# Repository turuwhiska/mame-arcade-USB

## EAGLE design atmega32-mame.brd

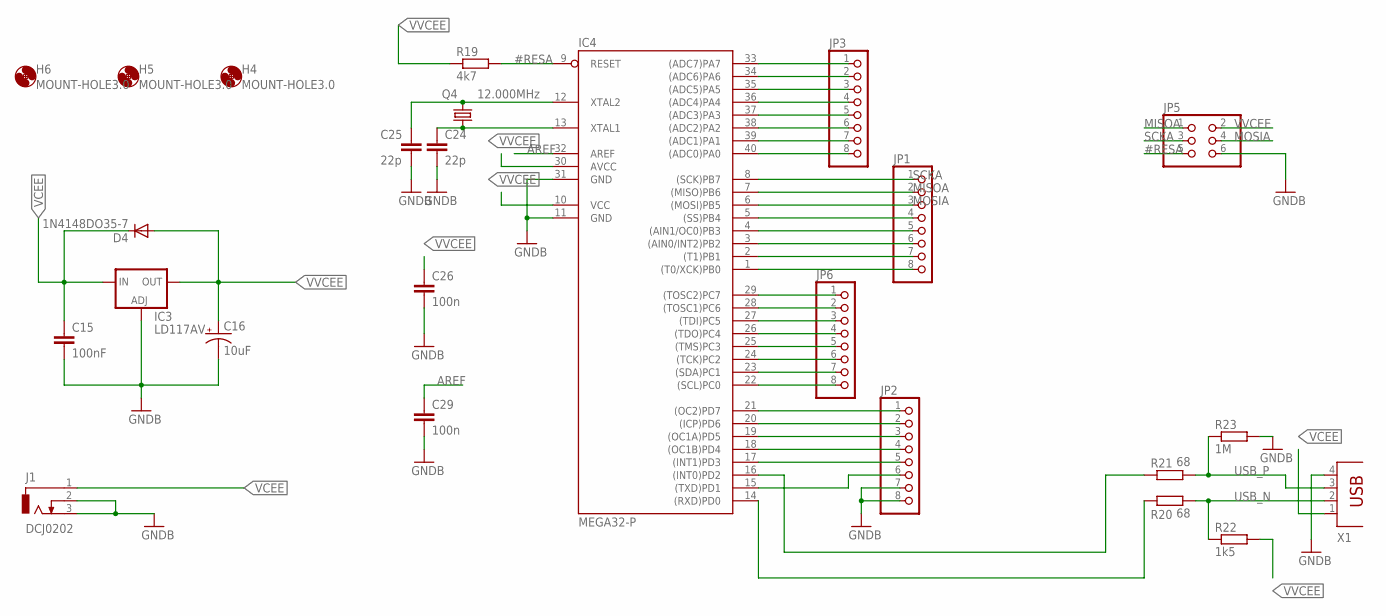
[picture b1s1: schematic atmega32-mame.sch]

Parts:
C15: 100nF; C025-025X050
C16: 10uF; E2,5-6E
C24, C25: 22p; C2.5-2
C26, C29: 100n; C5B2.5
D4: 1N4148DO35-7; DO35-7
H4, H5, H6: MOUNT-HOLE3.0; 3,0
IC3: LD117AV; TO220L1
IC4: MEGA32-P; DIL40
J1: DCJ0202
JP1, JP2, JP3, JP6: PINHD-1X8; 1X08
JP5: PINHD-2X3; 2X03
Q4: 12.000MHz; HC18U-V
R19: 4k7; 0207/10
R20, R21: 68; 0207/10
R22: 1k5; 0207/10
R23: 1M; 0207/10
X1: PN61729

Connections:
#RESA: IC4.9 (RESET), JP5.5, R19.2
AREF: C29.1, IC4.32 (AREF)
GND: C15.2, C16.-, C24.2, C25.2, C26.2, C29.2, IC3.1 (ADJ), IC4.11 (GND), IC4.31 (GND), J1.2, J1.3, JP2.7, JP2.8, JP5.6, R23.2, X1.4
MISOA: IC4.7 ((MISO)PB6), JP1.2, JP5.1
MOSIA: IC4.6 ((MOSI)PB5), JP1.3, JP5.4
unnamed: IC4.15 ((TXD)PD1), JP2.6
unnamed: IC4.16 ((INT0)PD2), R21.1
unnamed: IC4.14 ((RXD)PD0), R20.1
unnamed: C24.1, IC4.13 (XTAL1), Q4.1
unnamed: C25.1, IC4.12 (XTAL2), Q4.2
unnamed: IC4.21 ((OC2)PD7), JP2.1
unnamed: IC4.22 ((SCL)PC0), JP6.8
unnamed: IC4.23 ((SDA)PC1), JP6.7
unnamed: IC4.24 ((TCK)PC2), JP6.6
unnamed: IC4.25 ((TMS)PC3), JP6.5
unnamed: IC4.26 ((TDO)PC4), JP6.4
unnamed: IC4.27 ((TDI)PC5), JP6.3
unnamed: IC4.28 ((TOSC1)PC6), JP6.2
unnamed: IC4.29 ((TOSC2)PC7), JP6.1
unnamed: IC4.33 ((ADC7)PA7), JP3.1
unnamed: IC4.34 ((ADC6)PA6), JP3.2
unnamed: IC4.35 ((ADC5)PA5), JP3.3
unnamed: IC4.36 ((ADC4)PA4), JP3.4
unnamed: IC4.37 ((ADC3)PA3), JP3.5
unnamed: IC4.38 ((ADC2)PA2), JP3.6
unnamed: IC4.39 ((ADC1)PA1), JP3.7
unnamed: IC4.40 ((ADC0)PA0), JP3.8
unnamed: IC4.17 ((INT1)PD3), JP2.5
unnamed: IC4.18 ((OC1B)PD4), JP2.4
unnamed: IC4.19 ((OC1A)PD5), JP2.3
unnamed: IC4.20 ((ICP)PD6), JP2.2
unnamed: IC4.2 ((T1)PB1), JP1.7
unnamed: IC4.3 ((AIN0/INT2)PB2), JP1.6
unnamed: IC4.5 ((SS)PB4), JP1.4
unnamed: IC4.4 ((AIN1/OC0)PB3), JP1.5
unnamed: IC4.1 ((T0/XCK)PB0), JP1.8
SCKA: IC4.8 ((SCK)PB7), JP1.1, JP5.3
USB_N: R20.2, R22.1, X1.2
USB_P: R21.2, R23.1, X1.3
VCEE: C15.1, D4.C, IC3.3 (IN), J1.1, X1.1
VVCEE: C16.+, C26.1, D4.A, IC3.2 (OUT), IC4.10 (VCC), IC4.30 (AVCC), JP5.2, R19.1, R22.2

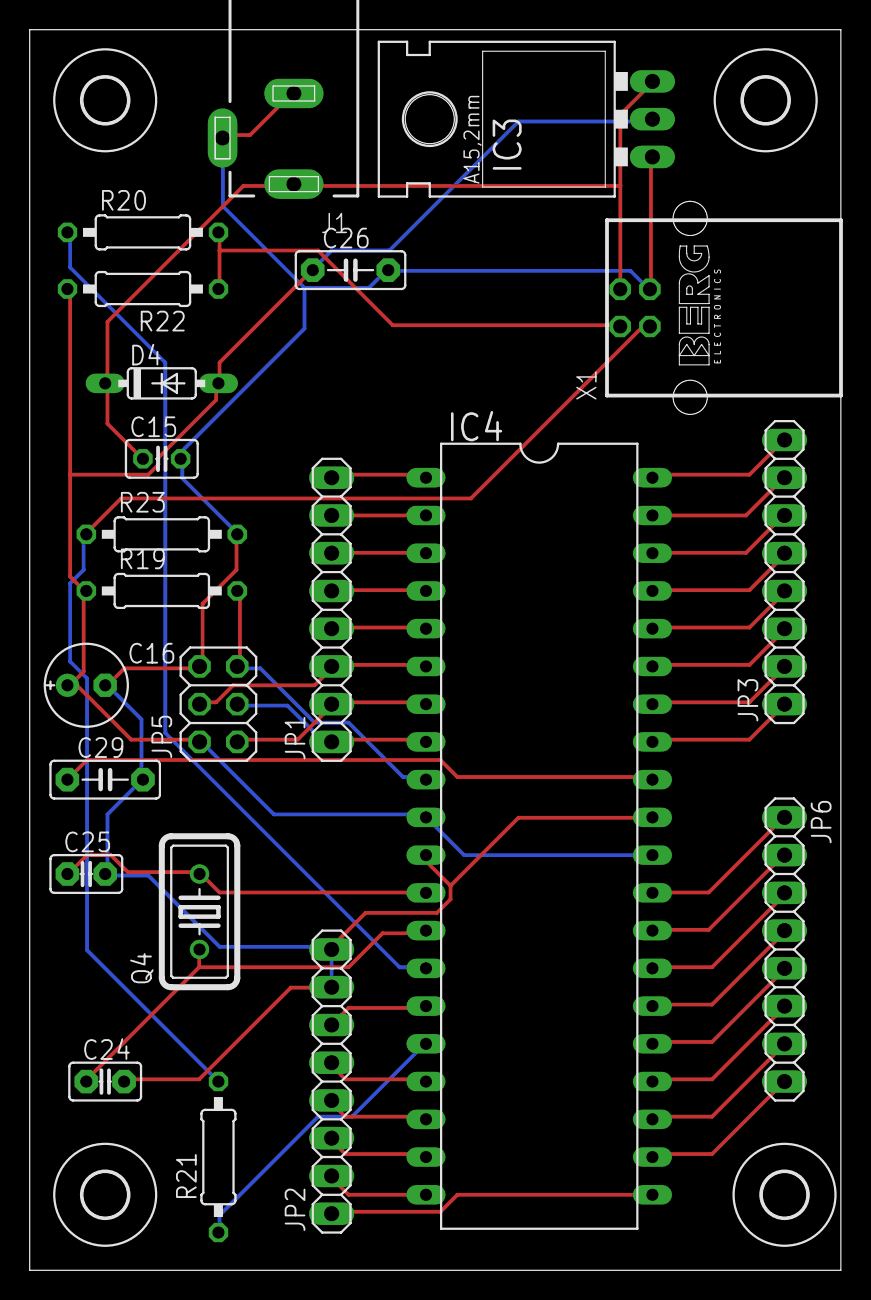
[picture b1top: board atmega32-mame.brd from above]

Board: 2 copper layers, 54.6 x 83.5 mm, 26 parts (0 on the bottom side), 41 nets.

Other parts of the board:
H1: MOUNT-HOLE3.0; 3,0
